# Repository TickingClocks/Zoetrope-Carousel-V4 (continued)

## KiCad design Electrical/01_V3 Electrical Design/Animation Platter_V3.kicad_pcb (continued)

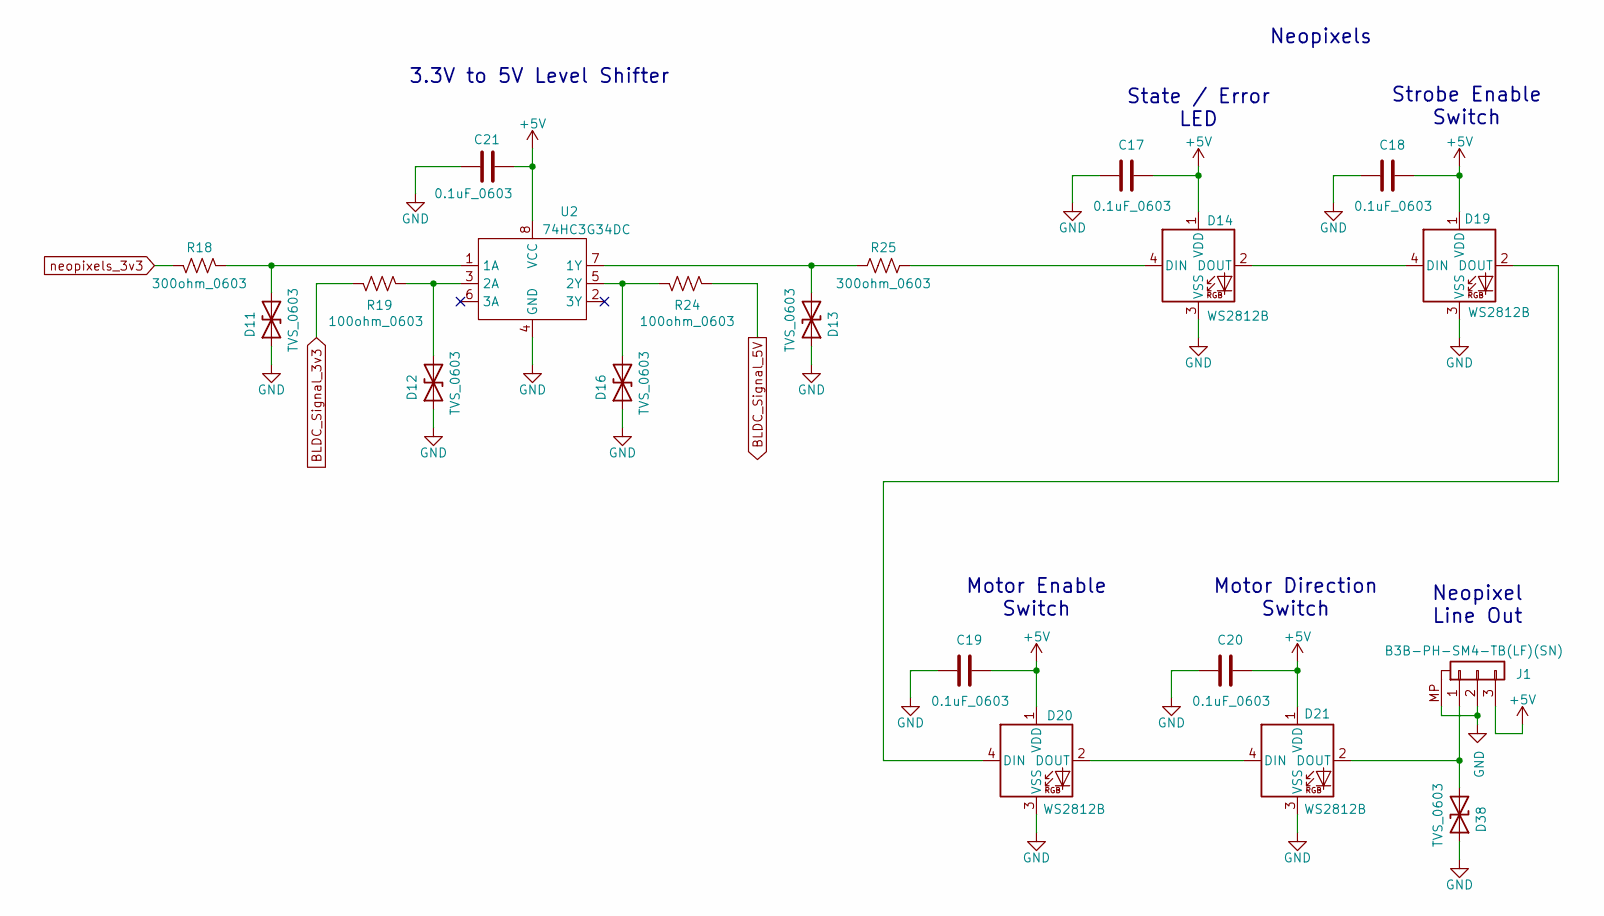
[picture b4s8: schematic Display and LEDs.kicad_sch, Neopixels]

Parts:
C17, C18, C19, C20, C21: 0.1uF_0603; C_0603_1608Metric
D11, D12, D13, D16, D38: TVS_0603; R_0603_1608Metric
D14, D19, D20, D21: WS2812B; LED_WS2812B_PLCC4_5.0x5.0mm_P3.2mm
J1: B3B-PH-SM4-TB(LF)(SN); JST_PH_B3B-PH-SM4-TB_1x03-1MP_P2.00mm_Vertical
R18, R25: 300ohm_0603; R_0603_1608Metric
R19, R24: 100ohm_0603; R_0603_1608Metric
U2: 74HC3G34DC

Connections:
unnamed: D11.2 (A2), R18.1, U2.1 (1A)
unnamed: D14.2 (DOUT), D19.4 (DIN)
unnamed: D19.2 (DOUT), D20.4 (DIN)
unnamed: D20.2 (DOUT), D21.4 (DIN)
neopixels_3v3: R18.2; also elsewhere on the board

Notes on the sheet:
State / Error LED
Neopixel Line Out
Strobe Enable Switch
Motor Direction Switch
Neopixels
3.3V to 5V Level Shifter
Motor Enable Switch

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
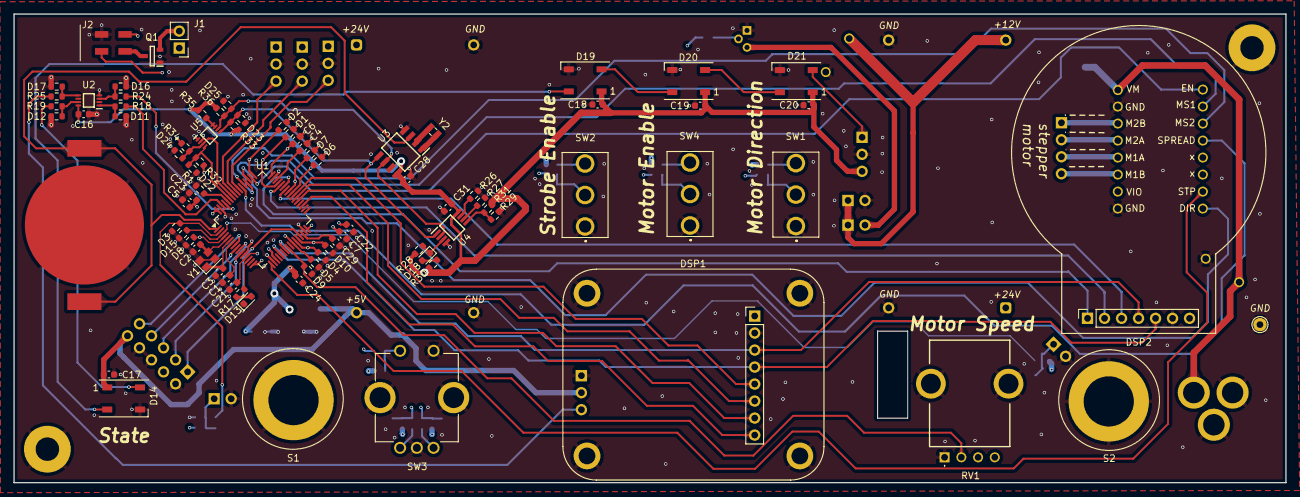
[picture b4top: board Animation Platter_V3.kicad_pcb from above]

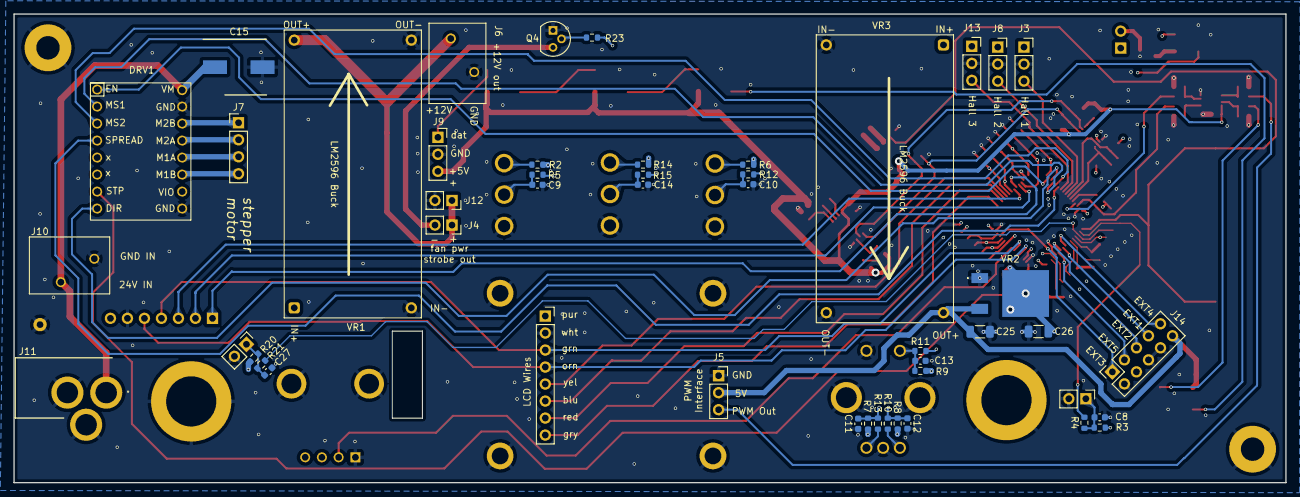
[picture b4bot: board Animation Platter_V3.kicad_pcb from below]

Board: 6 copper layers, 190.0 x 70.0 mm, 129 parts (45 on the bottom side), 92 nets.

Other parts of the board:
C16: 0.1uF_0603; C_0603_1608Metric
D17: TVS_0603; R_0603_1608Metric
DSP1: Conn_01x08; 240x280 LCD
DSP2: Conn_01x07; Circular LCD Display
J9: pinSocket x3; PinSocket_1x03_P2.54mm_Vertical
TP2: TestPoint; TestPoint_THTPad_D2.0mm_Drill1.0mm

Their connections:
LCD1_BL: DSP1.8; also elsewhere on the board
LCD1_CS: DSP1.5; also elsewhere on the board
LCD1_DC: DSP1.6; also elsewhere on the board
LCD1_RST: DSP1.7; also elsewhere on the board
LCD2_CS: DSP2.2; also elsewhere on the board
LCD2_DC: DSP2.3; also elsewhere on the board
LCD2_RST: DSP2.1; also elsewhere on the board
LCD_MOSI: DSP1.3, DSP2.4; also elsewhere on the board
LCD_SCK: DSP1.4, DSP2.5; also elsewhere on the board

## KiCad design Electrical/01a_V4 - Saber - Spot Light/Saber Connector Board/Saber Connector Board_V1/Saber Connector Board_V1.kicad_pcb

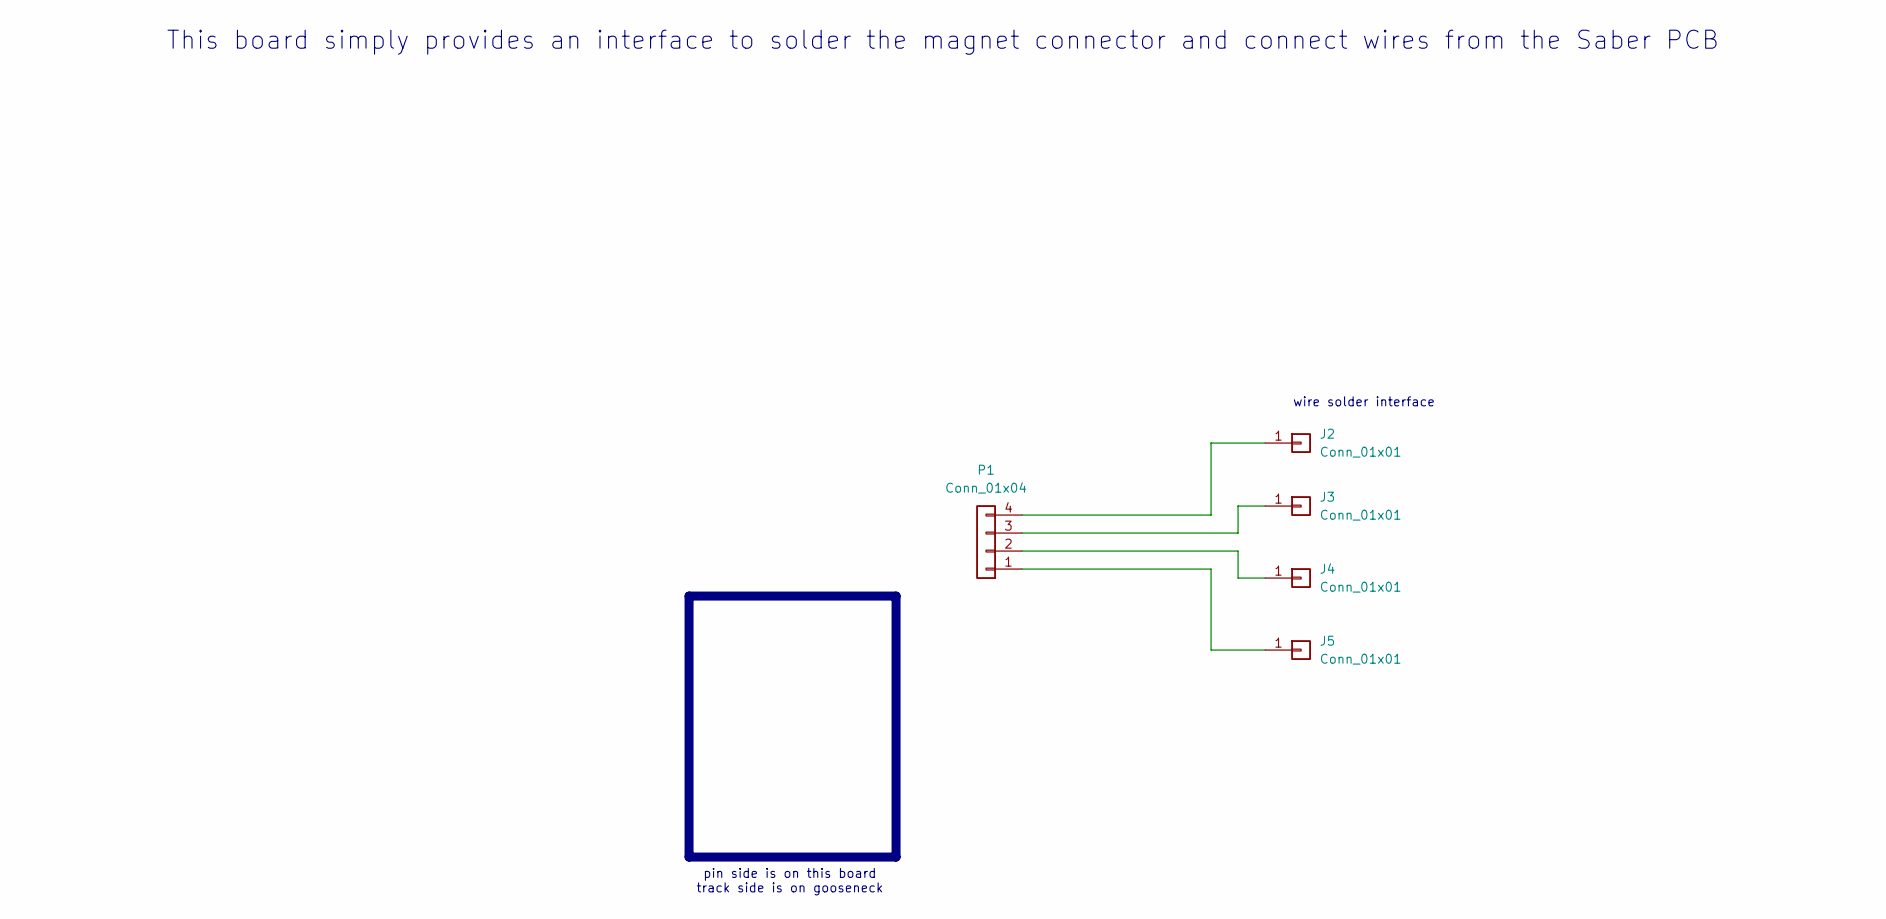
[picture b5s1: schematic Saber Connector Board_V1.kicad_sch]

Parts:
J2, J3, J4, J5: Conn_01x01; PinHeader_1x01_P2.54mm_Vertical
P1: Conn_01x04; Untitled

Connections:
unnamed: J2.1, P1.4
unnamed: J3.1, P1.3
unnamed: J4.1, P1.2
unnamed: J5.1, P1.1

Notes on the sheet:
pin side is on this board track side is on gooseneck
wire solder interface
This board simply provides an interface to solder the magnet connector and connect wires from the Saber PCB

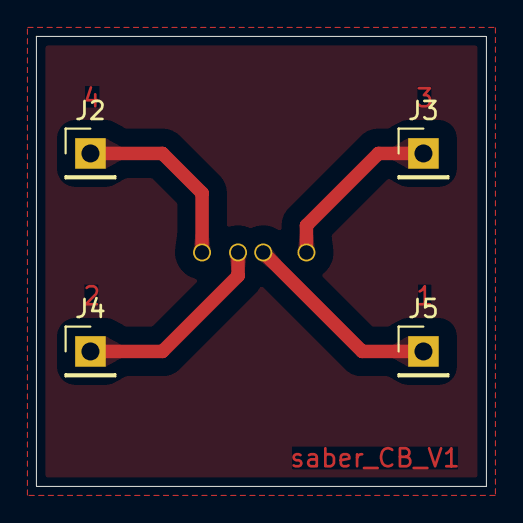
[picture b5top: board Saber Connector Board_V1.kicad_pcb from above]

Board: 2 copper layers, 25.0 x 25.0 mm, 5 parts (1 on the bottom side), 4 nets.

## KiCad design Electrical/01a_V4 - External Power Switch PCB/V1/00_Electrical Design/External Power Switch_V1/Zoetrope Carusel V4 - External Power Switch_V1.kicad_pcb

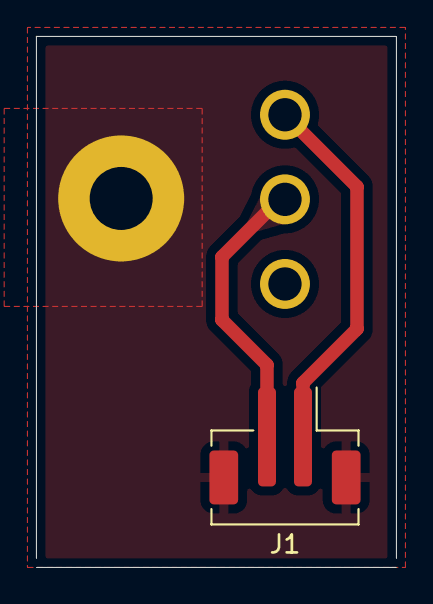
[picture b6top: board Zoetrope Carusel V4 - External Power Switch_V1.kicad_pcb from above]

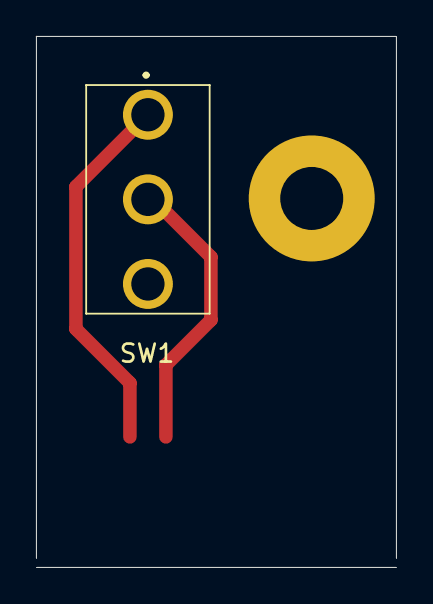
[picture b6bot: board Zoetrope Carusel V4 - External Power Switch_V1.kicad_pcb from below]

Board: 2 copper layers, 20.0 x 29.5 mm, 3 parts (2 on the bottom side), 3 nets.

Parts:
H2: MountingHole_Pad; 3mm_MH
J1: B2B-PH-SM4-TB(LF)(SN); JST_PH_B2B-PH-SM4-TB_1x02-1MP_P2.00mm_Vertical
SW1: 100SP1T1B4M2QE

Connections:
unnamed: J1.2, SW1.2 (B)
unnamed: J1.1, SW1.1 (C)
float: H2.1, J1.MP (Pin_1)

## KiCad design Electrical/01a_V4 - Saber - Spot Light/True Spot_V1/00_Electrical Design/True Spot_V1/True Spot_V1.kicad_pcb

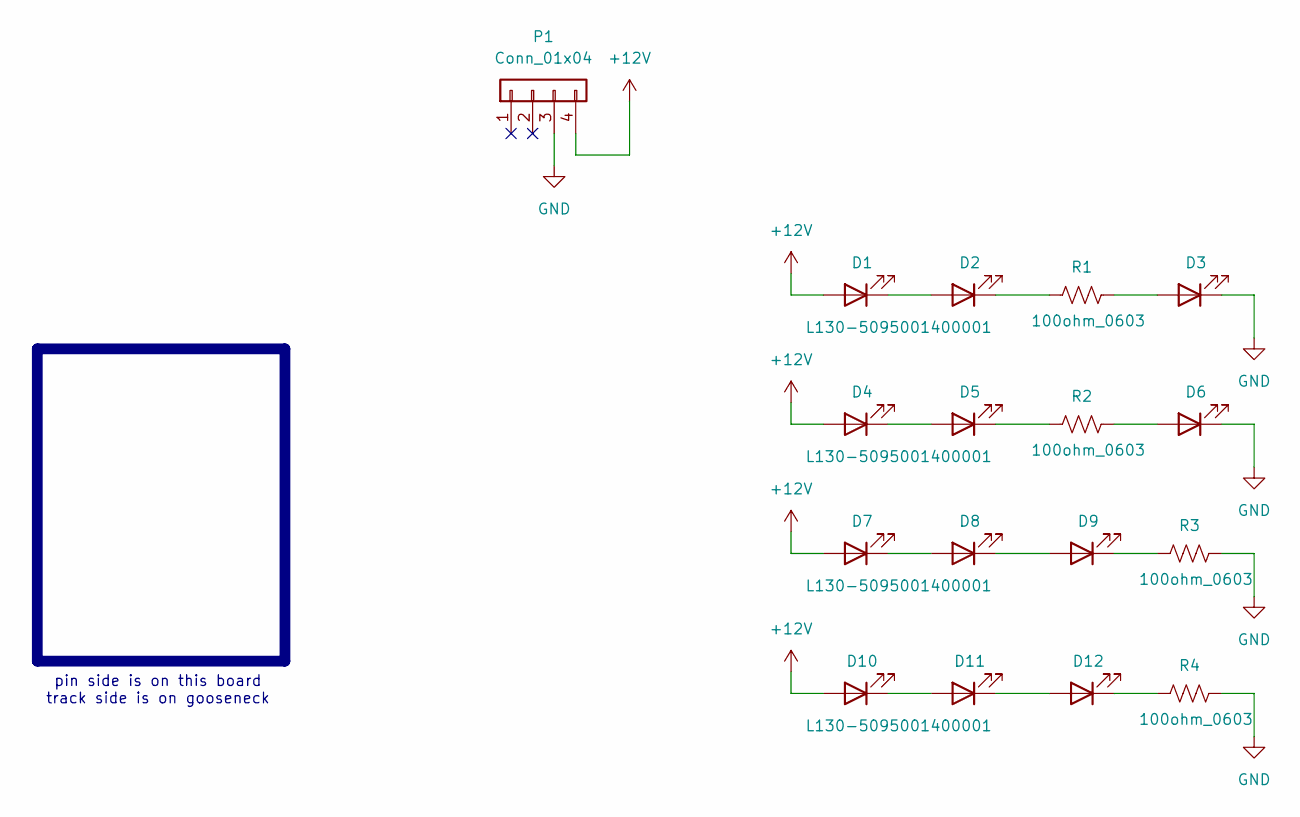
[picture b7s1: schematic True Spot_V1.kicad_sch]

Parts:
D1, D2, D3, D4, D5, D6, D7, D8, D9, D10, D11, D12: L130-5095001400001; L1305095001400001
P1: Conn_01x04; Untitled
R1, R2, R3, R4: 100ohm_0603; R_0603_1608Metric

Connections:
+12V: D1.2 (A), D4.2 (A), D7.2 (A), D10.2 (A), P1.4
GND: D3.1 (K), D6.1 (K), P1.3, R3.2, R4.2
unnamed: D1.1 (K), D2.2 (A)
unnamed: D2.1 (K), R1.1
unnamed: D3.2 (A), R1.2
unnamed: D4.1 (K), D5.2 (A)
unnamed: D5.1 (K), R2.1
unnamed: D6.2 (A), R2.2
unnamed: D7.1 (K), D8.2 (A)
unnamed: D8.1 (K), D9.2 (A)
unnamed: D9.1 (K), R3.1
unnamed: D10.1 (K), D11.2 (A)
unnamed: D11.1 (K), D12.2 (A)
unnamed: D12.1 (K), R4.1

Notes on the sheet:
pin side is on this board track side is on gooseneck

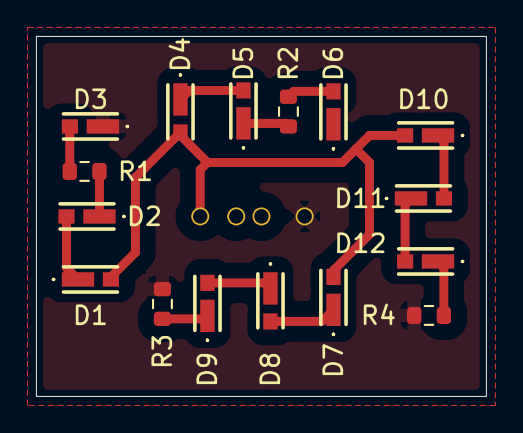
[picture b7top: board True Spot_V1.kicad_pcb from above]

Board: 2 copper layers, 25.0 x 20.0 mm, 17 parts (1 on the bottom side), 14 nets.

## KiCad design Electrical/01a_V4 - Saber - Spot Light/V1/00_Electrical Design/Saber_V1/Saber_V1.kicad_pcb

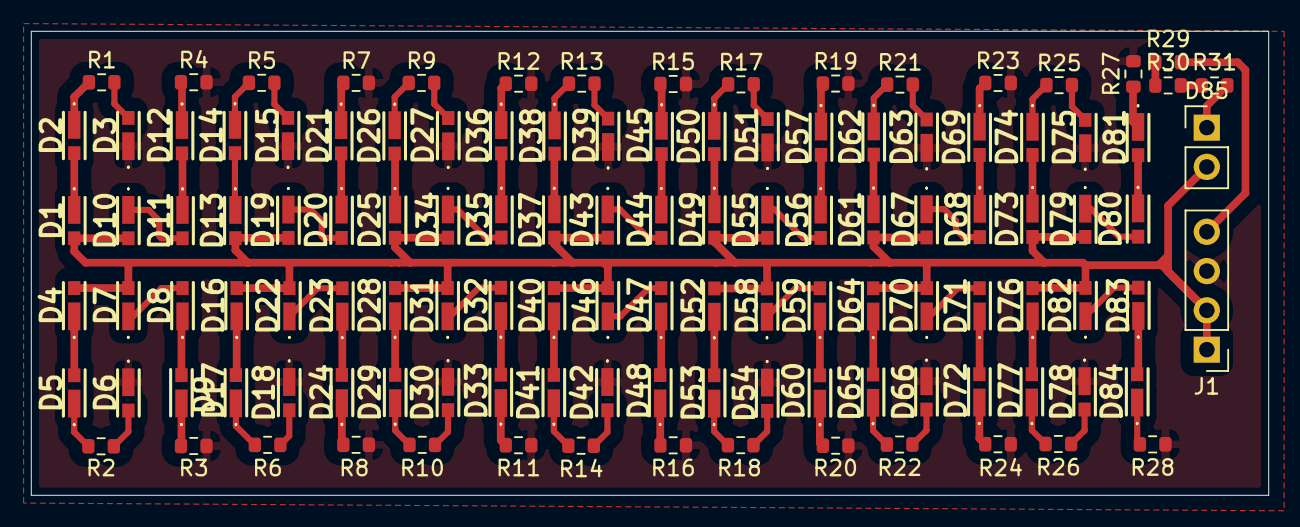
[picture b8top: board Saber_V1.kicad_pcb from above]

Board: 2 copper layers, 80.0 x 30.0 mm, 117 parts (0 on the bottom side), 90 nets.

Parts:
D1, D2, D3, D4, D5, D6, D7, D8, D9, D10, D11, D12, D13, D14, D15, D16, D17, D18, D19, D20, D21, D22, D23, D24, D25, D26, D27, D28, D29, D30, D31, D32, D33, D34, D35, D36, D37, D38, D39, D40, D41, D42, D43, D44, D45, D46, D47, D48, D49, D50, D51, D52, D53, D54, D55, D56, D57, D58, D59, D60, D61, D62, D63, D64, D65, D66, D67, D68, D69, D70, D71, D72, D73, D74, D75, D76, D77, D78, D79, D80, D81, D82, D83, D84: L130-5095001400001; L1305095001400001
D85: COB Filament LED; PinHeader_1x02_P2.54mm_Vertical
J1: Conn_01x04; PinHeader_1x04_P2.54mm_Vertical
R1, R2, R3, R4, R5, R6, R7, R8, R9, R10, R11, R12, R13, R14, R15, R16, R17, R18, R19, R20, R21, R22, R23, R24, R25, R26, R27, R28, R29, R30, R31: 100ohm_0603; R_0603_1608Metric

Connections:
+12V: D1.2 (A), D4.2 (A), D7.2 (A), D10.2 (A), D13.2 (A), D16.2 (A), D19.2 (A), D22.2 (A), D25.2 (A), D28.2 (A), D31.2 (A), D34.2 (A), D37.2 (A), D40.2 (A), D43.2 (A), D46.2 (A), D49.2 (A), D52.2 (A), D55.2 (A), D58.2 (A), D61.2 (A), D64.2 (A), D67.2 (A), D70.2 (A), D73.2 (A), D76.2 (A), D79.2 (A), D82.2 (A), D85.2 (A), J1.1, J1.2
GND: D3.1 (K), D6.1 (K), D15.1 (K), D18.1 (K), D27.1 (K), D30.1 (K), D39.1 (K), D42.1 (K), D51.1 (K), D54.1 (K), D63.1 (K), D66.1 (K), D75.1 (K), D78.1 (K), J1.3, R3.2, R4.2, R7.2, R8.2, R11.2, R12.2, R15.2, R16.2, R19.2, R20.2, R23.2, R24.2, R27.2, R28.2
GND2: J1.4, R29.2
unnamed: D1.1 (K), D2.2 (A)
unnamed: D2.1 (K), R1.1
unnamed: D3.2 (A), R1.2
unnamed: D4.1 (K), D5.2 (A)
unnamed: D5.1 (K), R2.1
unnamed: D6.2 (A), R2.2
unnamed: D7.1 (K), D8.2 (A)
unnamed: D8.1 (K), D9.2 (A)
unnamed: D9.1 (K), R3.1
unnamed: D10.1 (K), D11.2 (A)
unnamed: D11.1 (K), D12.2 (A)
unnamed: D12.1 (K), R4.1
unnamed: D13.1 (K), D14.2 (A)
unnamed: D14.1 (K), R5.1
unnamed: D15.2 (A), R5.2
unnamed: D16.1 (K), D17.2 (A)
unnamed: D17.1 (K), R6.1
unnamed: D18.2 (A), R6.2
unnamed: D19.1 (K), D20.2 (A)
unnamed: D20.1 (K), D21.2 (A)
unnamed: D21.1 (K), R7.1
unnamed: D22.1 (K), D23.2 (A)
unnamed: D23.1 (K), D24.2 (A)
unnamed: D24.1 (K), R8.1
unnamed: D25.1 (K), D26.2 (A)
unnamed: D26.1 (K), R9.1
unnamed: D27.2 (A), R9.2
unnamed: D28.1 (K), D29.2 (A)
unnamed: D29.1 (K), R10.1
unnamed: D30.2 (A), R10.2
unnamed: D31.1 (K), D32.2 (A)
unnamed: D32.1 (K), D33.2 (A)
unnamed: D33.1 (K), R11.1
unnamed: D34.1 (K), D35.2 (A)
unnamed: D35.1 (K), D36.2 (A)
unnamed: D36.1 (K), R12.1
unnamed: D37.1 (K), D38.2 (A)
unnamed: D38.1 (K), R13.1
unnamed: D39.2 (A), R13.2
unnamed: D40.1 (K), D41.2 (A)
unnamed: D41.1 (K), R14.1
unnamed: D42.2 (A), R14.2
unnamed: D43.1 (K), D44.2 (A)
unnamed: D44.1 (K), D45.2 (A)
unnamed: D45.1 (K), R15.1
unnamed: D46.1 (K), D47.2 (A)
unnamed: D47.1 (K), D48.2 (A)
unnamed: D48.1 (K), R16.1
unnamed: D49.1 (K), D50.2 (A)
unnamed: D50.1 (K), R17.1
unnamed: D51.2 (A), R17.2
unnamed: D52.1 (K), D53.2 (A)
unnamed: D53.1 (K), R18.1
unnamed: D54.2 (A), R18.2
unnamed: D55.1 (K), D56.2 (A)
unnamed: D56.1 (K), D57.2 (A)
unnamed: D57.1 (K), R19.1
unnamed: D58.1 (K), D59.2 (A)
unnamed: D59.1 (K), D60.2 (A)
unnamed: D60.1 (K), R20.1
unnamed: D61.1 (K), D62.2 (A)
unnamed: D62.1 (K), R21.1
unnamed: D63.2 (A), R21.2
unnamed: D64.1 (K), D65.2 (A)
unnamed: D65.1 (K), R22.1
unnamed: D66.2 (A), R22.2
unnamed: D67.1 (K), D68.2 (A)
unnamed: D68.1 (K), D69.2 (A)
unnamed: D69.1 (K), R23.1
unnamed: D70.1 (K), D71.2 (A)
unnamed: D71.1 (K), D72.2 (A)
unnamed: D72.1 (K), R24.1
unnamed: D73.1 (K), D74.2 (A)
unnamed: D74.1 (K), R25.1
unnamed: D75.2 (A), R25.2
unnamed: D76.1 (K), D77.2 (A)
unnamed: D77.1 (K), R26.1
unnamed: D78.2 (A), R26.2
unnamed: D79.1 (K), D80.2 (A)
unnamed: D80.1 (K), D81.2 (A)
unnamed: D81.1 (K), R27.1
unnamed: D82.1 (K), D83.2 (A)
unnamed: D83.1 (K), D84.2 (A)
unnamed: D84.1 (K), R28.1
unnamed: D85.1 (K), R31.1
unnamed: R29.1, R30.1
unnamed: R30.2, R31.2

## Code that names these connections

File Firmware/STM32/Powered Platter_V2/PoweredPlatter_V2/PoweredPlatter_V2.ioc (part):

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Mcu.Name=STM32C071KBTx
Mcu.Package=LQFP32_GP
Mcu.UserName=STM32C071KBTx
PA10.GPIOParameters=GPIO_Label
PA10.GPIO_Label=ledBLUE
PA10.Signal=GPIO_Output
PA11\ [PA9].GPIOParameters=GPIO_Label
PA11\ [PA9].GPIO_Label=ledGREEN
PA11\ [PA9].Signal=GPIO_Output
PA12\ [PA10].GPIOParameters=GPIO_Label
PA12\ [PA10].GPIO_Label=strobe
PA12\ [PA10].Signal=GPIO_Input
PA13.Mode=Serial_Wire
PA13.Signal=DEBUG_SWDIO
PA14-BOOT0.Mode=Serial_Wire
PA14-BOOT0.Signal=DEBUG_SWCLK
PA15.GPIOParameters=GPIO_Label
PA15.GPIO_Label=led8
PA15.Signal=GPIO_Output
PA2.GPIOParameters=GPIO_Label
PA2.GPIO_Label=neopixel
PA2.Signal=GPIO_Output
PA4.GPIOParameters=GPIO_Label
PA4.GPIO_Label=led1
PA4.Signal=GPIO_Output
PA5.GPIOParameters=GPIO_Label
PA5.GPIO_Label=led2
PA5.Signal=GPIO_Output
PA6.GPIOParameters=GPIO_Label
PA6.GPIO_Label=led3
PA6.Signal=GPIO_Output
PA7.GPIOParameters=GPIO_Label
PA7.GPIO_Label=led4
PA7.Signal=GPIO_Output
PA9.GPIOParameters=GPIO_Label
PA9.GPIO_Label=ledRED
PA9.Signal=GPIO_Output
PB0.GPIOParameters=GPIO_Label
PB0.GPIO_Label=led5
PB0.Signal=GPIO_Output
PB1.GPIOParameters=GPIO_Label
PB1.GPIO_Label=led6
PB1.Signal=GPIO_Output
PB2.GPIOParameters=GPIO_Label
PB2.GPIO_Label=led7
PB2.Signal=GPIO_Output
PB3.GPIOParameters=GPIO_Label
PB3.GPIO_Label=led9
PB3.Signal=GPIO_Output
PB4.GPIOParameters=GPIO_Label
PB4.GPIO_Label=led10
PB4.Signal=GPIO_Output
PB5.GPIOParameters=GPIO_Label
PB5.GPIO_Label=led11
PB5.Signal=GPIO_Output
PB6.GPIOParameters=GPIO_Label
PB6.GPIO_Label=led12
PB6.Signal=GPIO_Output
PB7.GPIOParameters=GPIO_Label
PB7.GPIO_Label=led13
PB7.Signal=GPIO_Output
PB8.GPIOParameters=GPIO_Label
PB8.GPIO_Label=led14
PB8.Signal=GPIO_Output
PB9.GPIOParameters=GPIO_Label
PB9.GPIO_Label=IR_input
PB9.Signal=GPIO_Input
RCC.HSE_VALUE=8000000
RCC.SYSCLKFreq_VALUE=48000000
board=custom

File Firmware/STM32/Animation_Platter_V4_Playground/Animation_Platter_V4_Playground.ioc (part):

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Mcu.Name=STM32F446R(C-E)Tx
Mcu.Package=LQFP64
Mcu.UserName=STM32F446RETx
PA0-WKUP.Signal=ADCx_IN0
PA1.Signal=S_TIM2_CH2
PA13.Mode=Serial_Wire
PA13.Signal=SYS_JTMS-SWDIO
PA14.Mode=Serial_Wire
PA14.Signal=SYS_JTCK-SWCLK
PA5.Mode=PWM Generation1 CH1N
PA5.Signal=TIM8_CH1N
PA8.Signal=S_TIM1_CH1
PA9.Signal=S_TIM1_CH2
PB6.GPIOParameters=GPIO_PuPd
PB6.GPIO_PuPd=GPIO_PULLDOWN
PB6.Signal=S_TIM4_CH1
PB7.Mode=I2C
PB7.Signal=I2C1_SDA
PB8.Mode=I2C
PB8.Signal=I2C1_SCL
PC0.GPIOParameters=GPIO_PuPd,GPIO_ModeDefaultEXTI
PC0.GPIO_ModeDefaultEXTI=GPIO_MODE_IT_FALLING
PC0.GPIO_PuPd=GPIO_PULLUP
PC0.Signal=GPXTI0
PC10.Mode=Asynchronous
PC10.Signal=UART4_TX
PC11.Mode=Asynchronous
PC11.Signal=UART4_RX
PC12.Mode=Asynchronous
PC12.Signal=UART5_TX
PC13.GPIOParameters=GPIO_Label
PC13.GPIO_Label=U10_int
PC13.Signal=GPIO_Input
PC4.GPIOParameters=GPIO_Label
PC4.GPIO_Label=U7_int
PC4.Signal=GPIO_Input
PC5.GPIOParameters=GPIO_Label
PC5.GPIO_Label=U3_int
PC5.Signal=GPIO_Input
PC6.GPIOParameters=GPIO_Label
PC6.GPIO_Label=testLED3
PC6.Signal=GPIO_Output
PC7.GPIOParameters=GPIO_Label
PC7.GPIO_Label=testLED2
PC7.Signal=GPIO_Output
PC8.GPIOParameters=GPIO_Label
PC8.GPIO_Label=testLED1
PC8.Signal=GPIO_Output
PD2.Mode=Asynchronous
PD2.Signal=UART5_RX
PH0-OSC_IN.Mode=HSE-External-Oscillator
PH0-OSC_IN.Signal=RCC_OSC_IN
PH1-OSC_OUT.Mode=HSE-External-Oscillator
PH1-OSC_OUT.Signal=RCC_OSC_OUT
RCC.HSE_VALUE=16000000
RCC.SYSCLKFreq_VALUE=180000000
RCC.SYSCLKSource=RCC_SYSCLKSOURCE_PLLCLK
board=custom

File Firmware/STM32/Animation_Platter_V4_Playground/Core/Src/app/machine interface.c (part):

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    sys->zoetropeEnabled = 0; //zoetrope disabled by default
    sys->strobeOnTime_ms = 0;
    sys->strobeOnTime_us = 0;
    sys->strobeOffTime_ms = 0; //this is calculated with sliceTime and is dependint on total slice time and strobe on time
    sys->sliceCount = 20; //default to 20 slices
    sys->sliceIndex = 0; //start at slice 0
    sys->platterRotationPeriod_ms = 0;
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    sys->sliceTime_ms = 0;
    //new strobe mode variables
    sys->strobeSrcClockValue = 45000000; //45MHz clock source for timer 4 (full speed, APB1)
    sys->strobePSCValue = 0; //calculated strobe PSC value for PWM output
    sys->strobeARRValue = 1000; //calculated strobe ARR value for PWM output - attempting to keep this at 1000 for simpler CCR control
    sys->strobeCCRValue = 10; //calculated strobe CCR value for PWM output - value 0 to ARR
    sys->strobeMode = 0; //default strobe mode (classic)
    sys->strobeEnabled = 0; //strobe disabled by default
    //reset the strobe PWM arrays
    for(int i = 0; i < 256; i++){
        sys->shadowStrobePWMArray[i] = 0;
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
      //write to the I/O expander outputs and LEDs
      HAL_GPIO_WritePin(GPIOC, testLED1_Pin, sys->blueLED);
      HAL_GPIO_WritePin(GPIOC, testLED2_Pin, sys->redLED);
      HAL_GPIO_WritePin(GPIOC, testLED3_Pin, sys->greenLED);

      //update the data value for all three I2C I/O expanders
      TCA9534_updateData(&TCA_port1, zoetrope_I2CPortByte(sys, 1));
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    //note the prev sensor state
    prevhallSensor1State = sys->hallSensor1;
    //read the state of hall sensor 1 and assign the system variable
    sys->hallSensor1 = HAL_GPIO_ReadPin(GPIOC, GPIO_PIN_0); //PC0 == hall sensor 1 input

    //see if the state of the sensor has changed
    if(sys->hallSensor1 != prevhallSensor1State){
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            sys->hallSensor1LastTime_us = currentTime_maxSpeed; //update the last time variable
            sys->platterRotationPeriod_us = sys->hallSensor1Period_us; //for now, platter period == hall sensor period || not actually us, update this later
            zoetrope_calculateFramePeriod(sys); //calculate the frame pulse period using system variables
            sys->strobePWMCalculateRequired = 1; //flag to recalculate strobe PWM settings -- do in interrupt in future
        }
    }
}
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    uint8_t digit4CurrentSlice = 0;
    uint8_t digit5CurrentSlice = 0;

    uint8_t digit1Check = 0; //flag if segment exists in displayed character - set strobe
    uint8_t digit2Check = 0;
    uint8_t digit3Check = 0;
    uint8_t digit4Check = 0;
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            }
            
        }else{
            sys->shadowStrobePWMArray[k] = 0; //set strobe OFF for this slice
            //sys->shadowStrobePWMArray[k] = sys->strobeCCRValue; //this turns everything on - not truly what I want, just test
        }
    }
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                //stateMachine_state 10 will reset speed to zero, setting the calculate variable here so the value is updated
                sys->platterRotationPeriod_us = 0;
                sys->platterRotationPeriod_ms = 0;
                sys->strobePWMCalculateRequired = 1; //flag to recalculate strobe PWM settings -- do in interrupt in future
                sys->demoCounter = 0; //reset demo counter
            }   

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                //stateMachine_state 10 will reset speed to zero, setting the calculate variable here so the value is updated
                sys->platterRotationPeriod_us = 0;
                sys->platterRotationPeriod_ms = 0;
                sys->strobePWMCalculateRequired = 1; //flag to recalculate strobe PWM settings -- do in interrupt in future
                sys->demoCounter = 0; //reset demo counter
            }       

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    //15 = NFC write tag mode (**********)
    //100 = normal (non-NFC) operation mode (strobe running, motor running; all strobe and motor functions decided here)
    //101 = normal (NFC settings) operation mode (strobe running, motor running; all strobe and motor functions decided here)
    //200 = spindown mode (strobe off, motor spindown; mandatory for high speed platters)
    //1000 = error state

    switch(sys->stateMachine_state){
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                //motor is not enabled - reset some variables
                sys->NFCDetectedFlag = 0; //clear NFC detected flag
                sys->blueLED = 0; //turn off blue LED to indicate NFC tag not found
                //sys->strobePWMCalculateRequired = 1; //flag to recalculate strobe PWM settings -- do in interrupt in future
                sys->nfcHallSensorReadCount = 0; //clear hall sensor read count for NFC scanning
                //reset speed
                sys->platterRotationPeriod_us = 0;
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                        //sys->hallSensor1LastTime_us = currentTime_us; //update the last time variable
                        sys->platterRotationPeriod_us = sys->hallSensor1Period_us; //for now, platter period == hall sensor period
                        zoetrope_calculateFramePeriod(sys); //calculate the frame pulse period using system variables
                        sys->strobePWMCalculateRequired = 1; //flag to recalculate strobe PWM settings -- do in interrupt in future
                        //reset tim5 in case that is my problem
                        TIM5->CNT = 0;
                        sys->hallSensor1LastTime_us = 0;
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                        //sys->hallSensor1LastTime_us = currentTime_us; //update the last time variable
                        sys->platterRotationPeriod_us = sys->hallSensor1Period_us; //for now, platter period == hall sensor period
                        zoetrope_calculateFramePeriod(sys); //calculate the frame pulse period using system variables
                        sys->strobePWMCalculateRequired = 1; //flag to recalculate strobe PWM settings -- do in interrupt in future
                        //reset tim5 in case that is my problem
                        TIM5->CNT = 0;
                        sys->hallSensor1LastTime_us = 0;
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                    //sys->hallSensor1LastTime_us = currentTime_us; //update the last time variable
                    sys->platterRotationPeriod_us = sys->hallSensor1Period_us; //for now, platter period == hall sensor period
                    zoetrope_calculateFramePeriod(sys); //calculate the frame pulse period using system variables
                    sys->strobePWMCalculateRequired = 1; //flag to recalculate strobe PWM settings -- do in interrupt in future
                    //reset tim5 in case that is my problem
                    TIM5->CNT = 0;
                    sys->hallSensor1LastTime_us = 0;
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        case 0: //1/8 step
            //MS1 = LOW
            //MS2 = LOW
            sys->motor_MS1 = 0;
            sys->motor_MS2 = 0;
            break;
        case 1: //1/16 step
            //MS1 = HIGH
            //MS2 = HIGH
            sys->motor_MS1 = 1;
            sys->motor_MS2 = 1;
            break;
        case 2: //1/32 step
            //MS1 = HIGH
            //MS2 = LOW
            sys->motor_MS1 = 1;
            sys->motor_MS2 = 0;
            break;      
        case 3: //1/64 step
            //MS1 = LOW
            //MS2 = HIGH
            sys->motor_MS1 = 0;
            sys->motor_MS2 = 1;
            break;
    }

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
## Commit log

2026-02-22 remove large files and apply gitignore
2026-02-22 adding OneNote export file
2026-02-26 updates to schematic to document circuits and electrical components connected to, but not mounted on, the PCB
2026-03-07 new power switch PCB design
2026-03-08 adding v2 of the switch pcb. reduced file name lengths to work with git. re-upload after accidentally clearing the repository
2026-03-08 adding photoeye PCB files
2026-03-09 adding the photoEyeOnly PCB files
2026-03-09 fixing the crossed wire for the photo sensor. deleting the old CNC jobs. Re-exporting gerbers and schematics. Re-mill with new files
2026-03-10 updates and cnc files to photo eye pcbs
2026-03-15 updates to schematic to document outside components. Plans for additional electrical features requiring desiging a few more PCBs
2026-03-15 main schematic tweaks. Started the 'Saber' PCB which is the new end effector for the strobe light. Schematic nearly finished. Need to create footprint for LEDs and layout the board to be CNC milled.
2026-03-15 designed the saber PCB, exported the files. Time to attempt to CNC and test it
2026-03-29 several incremental updates - adding True Spot spotlight effector PCB
2026-04-05 routine addition, incremental improvments and updates
2026-05-01 fresh repo
2026-05-01 ignore kicad .history folders -messes with git of overall project
2026-05-02 second powered platter main PCB designed and ready for CNC milling
2026-05-02 adding LED Blade for Powered Platter 2. PCBs are being milled, 3D print needs to still be designed
2026-05-04 adding HTML BOMs for Powered Platter V2 - building hardware now
2026-05-05 small updates - pushing to move to other computer
2026-05-07 adding updated 3D print frame for powered platter v2
2026-05-07 adding base project and cubeMX for powered platter v2
2026-05-08 built and validated powered platter_V2 design. this update includes the first program for this hardware. this program will makes a display 150x7 pixels wrapped around the entire platter. It can tell 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
2026-05-12 fixed bug where extra LEDs were turned ON
2026-05-12 saving for the evening
2026-05-14 maxed out timer5 to calculate time at the finest resolution possible (1us / 45). *45 additions have been added throughout to fix other calculations. Would be worth updating or adding a few more varia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
2026-05-17 incremental updates to powered platter program, creating a font to be able to be used. Capitol fonts done, not tested. Lower case fonts started. Numbers to be added. Saving prior to my work trip
